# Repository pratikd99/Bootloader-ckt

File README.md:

# Bootloader-ckt
The ckt for Bootloader is made and schematic and board files are added.

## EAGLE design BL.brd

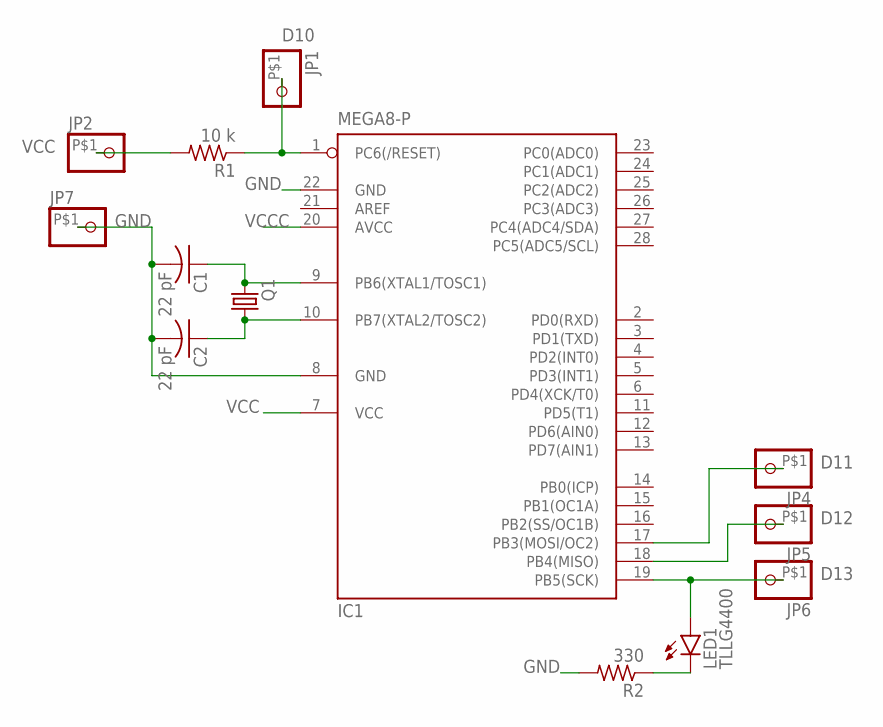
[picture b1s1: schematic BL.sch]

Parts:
C1, C2: 22 pF; C025-030X050
IC1: MEGA8-P; DIL28-3
JP1, JP2, JP4, JP5, JP6, JP7: PINHD-1X1-BIGPOGO; 1X1-BIGPOGO
LED1: TLLG4400; LED3MM
Q1: CRYSTALHC49S; HC49/S
R1: 10 k; 0204/7
R2: 330; 0204/7

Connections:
D10: IC1.1 (PC6(/RESET)), JP1.P$1, R1.1
D11: IC1.17 (PB3(MOSI/OC2)), JP4.P$1
D12: IC1.18 (PB4(MISO)), JP5.P$1
D13: IC1.19 (PB5(SCK)), JP6.P$1, LED1.A
GND: C1.2, C2.2, IC1.8 (GND), IC1.22 (GND), JP7.P$1, R2.2
unnamed: C1.1, IC1.9 (PB6(XTAL1/TOSC1)), Q1.2
unnamed: C2.1, IC1.10 (PB7(XTAL2/TOSC2)), Q1.1
unnamed: LED1.K (C), R2.1
VCC: IC1.7 (VCC), JP2.P$1, R1.2
VCCC: IC1.20 (AVCC)

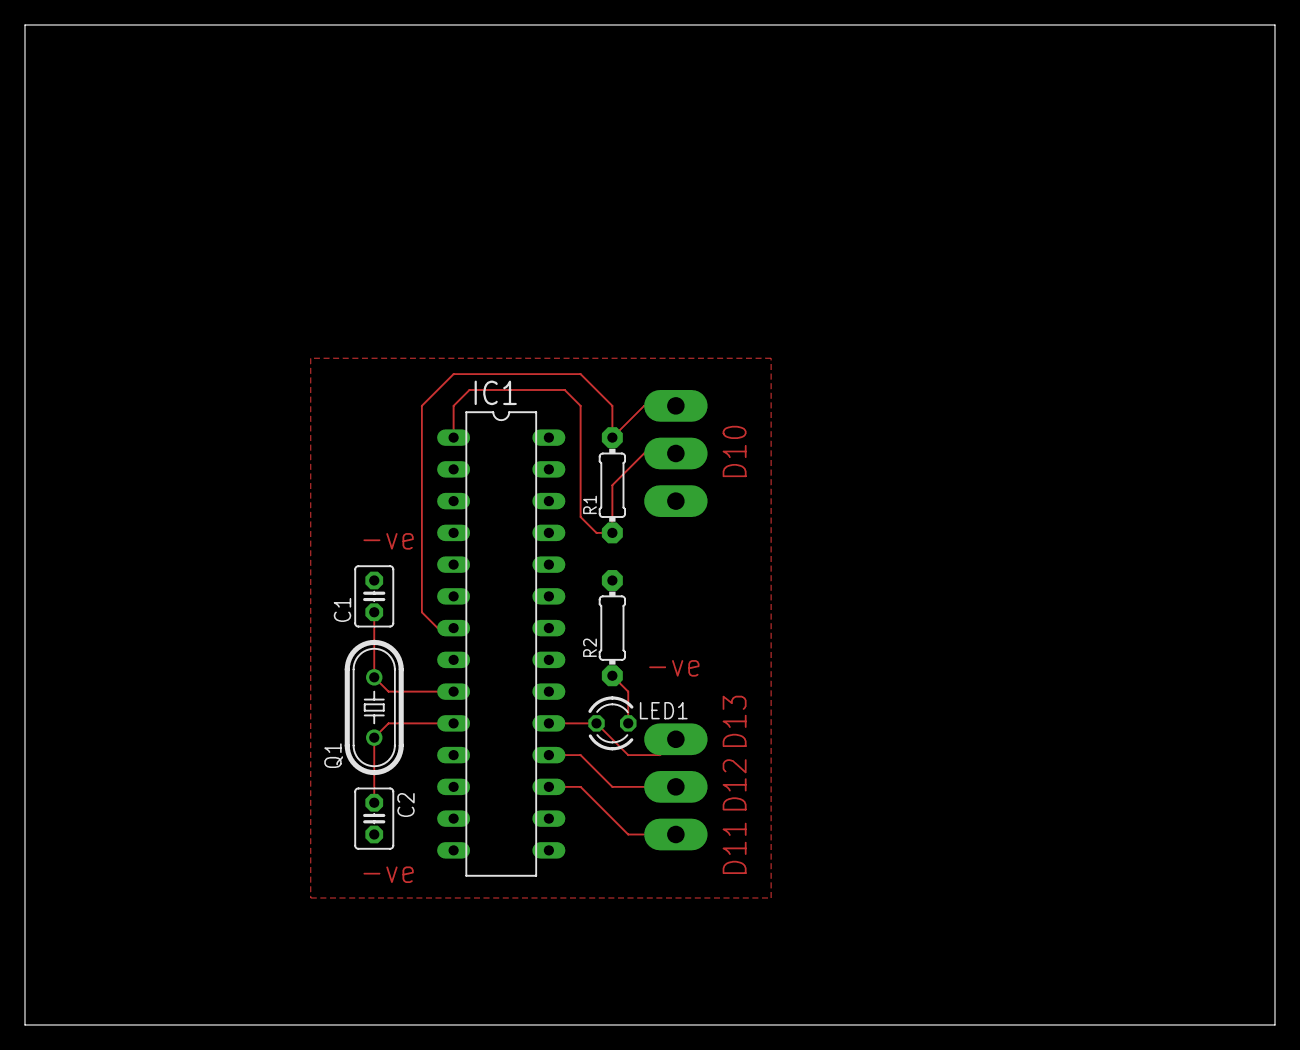
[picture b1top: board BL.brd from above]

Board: 2 copper layers, 100.0 x 80.0 mm, 13 parts (0 on the bottom side), 9 nets.
